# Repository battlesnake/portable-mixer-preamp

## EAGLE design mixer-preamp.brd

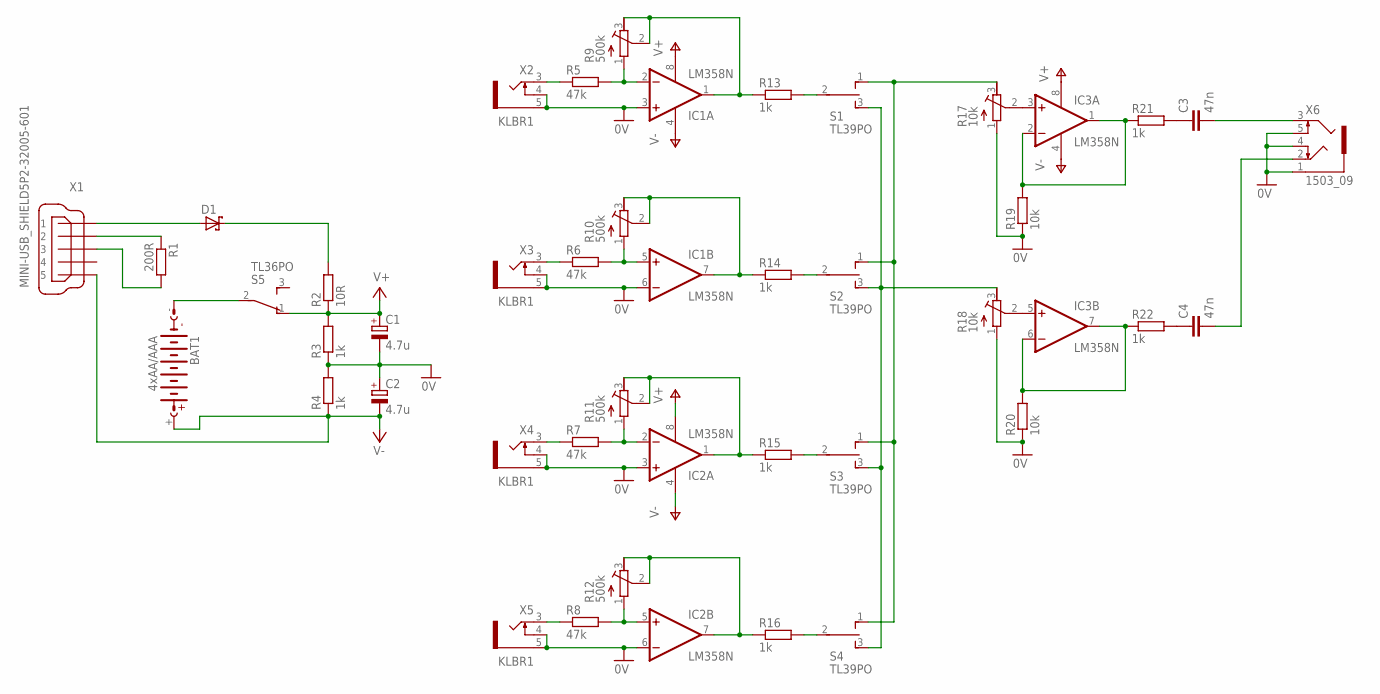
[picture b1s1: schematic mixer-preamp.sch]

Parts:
BAT1: 4xAA/AAA; AB9V
C1, C2: 4.7u; E5-5
C3, C4: 47n; C025-024X044
D1: SCHOTTKY-DIODEDO35-7; DO35-7
IC1, IC2, IC3: LM358N; DIL08
R1: 200R; 0204V
R2: 10R; 0204/7
R3, R4: 1k; 0204V
R5, R6, R7, R8: 47k; 0207/10
R9, R10, R11, R12: 500k; RTRIM3296W
R13, R14, R15, R16, R21, R22: 1k; 0207/10
R17, R18: 10k; RTRIM3296W
R19, R20: 10k; 0207/10
S1, S2, S3, S4: TL39PO; TL3XPO
S5: TL36PO; TL3XPO
X1: MINI-USB_SHIELD5P2-32005-601; 32005-601
X2, X3, X4, X5: KLBR1
X6: 1503_09

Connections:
0V: C1.-, C2.+, IC1.3 (+IN), IC1.6 (-IN), IC2.3 (+IN), IC2.6 (-IN), R3.1, R4.2, R17.1 (A), R18.1 (A), R19.1, R20.1, X2.4, X2.5, X3.4, X3.5, X4.4, X4.5, X5.4, X5.5, X6.1, X6.4, X6.5
unnamed: R13.2, S1.2
unnamed: IC3.5 (+IN), R18.2 (S)
unnamed: IC1.2 (-IN), R5.2, R9.1 (A)
unnamed: R5.1, X2.3
unnamed: IC3.6 (-IN), IC3.7 (OUT), R20.2, R22.1
unnamed: IC1.1 (OUT), R9.2 (S), R9.3 (E), R13.1
unnamed: R14.2, S2.2
unnamed: IC1.5 (+IN), R6.2, R10.1 (A)
unnamed: IC3.3 (+IN), R17.2 (S)
unnamed: C4.2, X6.2
unnamed: R6.1, X3.3
unnamed: C3.1, R21.2
unnamed: IC1.7 (OUT), R10.2 (S), R10.3 (E), R14.1
unnamed: C4.1, R22.2
unnamed: R15.2, S3.2
unnamed: IC2.2 (-IN), R7.2, R11.1 (A)
unnamed: C3.2, X6.3
unnamed: D1.C, R2.2
unnamed: R7.1, X4.3
unnamed: IC2.1 (OUT), R11.2 (S), R11.3 (E), R15.1
unnamed: IC3.1 (OUT), IC3.2 (-IN), R19.2, R21.1
unnamed: R1.1, X1.2
unnamed: R16.2, S4.2
unnamed: R1.2, X1.3
unnamed: IC2.5 (+IN), R8.2, R12.1 (A)
unnamed: R8.1, X5.3
unnamed: IC2.7 (OUT), R12.2 (S), R12.3 (E), R16.1
unnamed: R18.3 (E), S1.3 (S), S2.3 (S), S3.3 (S), S4.3 (S)
unnamed: R17.3 (E), S1.1 (O), S2.1 (O), S3.1 (O), S4.1 (O)
unnamed: D1.A, X1.1
unnamed: BAT1.-, S5.2
V+: C1.+, IC1.8 (V+), IC2.8 (V+), IC3.8 (V+), R2.1, R3.2, S5.1 (O)
V-: BAT1.+, C2.-, IC1.4 (V-), IC2.4 (V-), IC3.4 (V-), R4.1, X1.5

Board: 2 copper layers, 42 parts (0 on the bottom side), 34 nets, no tracks yet.

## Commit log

2015-06-04 Initial (schematics out of date)
2015-06-07 rc-filter charting
2015-06-08 Schematic added
2015-06-08 SVG schematics (Kicad fucked up the part numbers though)
2015-06-15 Boost stage fixed
2015-06-29 Test signal generator
2015-06-29 Alsa-play fork/exec launcher spun into separate file
2015-06-29 Preamp possibly fixed
2015-06-30 Improved preamp
2015-06-30 Kicad replaces library when saving, breaks hardlinks. Updated mark.lib manually.
2015-06-30 Cleaned up labels
2015-06-30 Output stage improved
2015-06-30 Makefile updates hardlink
